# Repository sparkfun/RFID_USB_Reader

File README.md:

SparkFun RFID USB Reader
=========================

[*SparkFun RFID USB Reader (SEN-09963)*](https://www.sparkfun.com/products/9963)

The SparkFun RFID USB Reader is a simple to use, USB to serial base unit for the ID-3LA, ID-12LA, and ID-20LA readers.

Documentation
-------------
- **[Hookup Guide](https://learn.sparkfun.com/tutorials/sparkfun-rfid-starter-kit-hookup-guide)** - The hookup guide for the SparkFun RFID USB Reader

Repository Contents
-------------------
- **[/Hardware](/Hardware/)** - Hardware design files (.brd, .sch)
- **[/Production](/Production/)** - Production files

Product Variants
----------------
- [SEN-28020](https://www.sparkfun.com/sparkfun-rfid-usb-c-reader.html) - USB-C connector and CH340C converter
- [SEN-09963](https://www.sparkfun.com/sparkfun-rfid-usb-reader.html) - Original product *(w/ USB mini-B connector and FTDI converter)*

Version History
---------------
- [v10](https://github.com/sparkfun/RFID_USB_Reader/releases/tag/v10) - Initial Release

License Information
-------------------

This product is ***open source***!

Please review the [`LICENSE.md`](./LICENSE.md) file for license information.

If you have any questions or concerns about licensing, please contact technical support on our [SparkFun forums](https://forum.sparkfun.com/viewforum.php?f=152).

Distributed as-is; no warranty is given.

- Your friends at SparkFun.

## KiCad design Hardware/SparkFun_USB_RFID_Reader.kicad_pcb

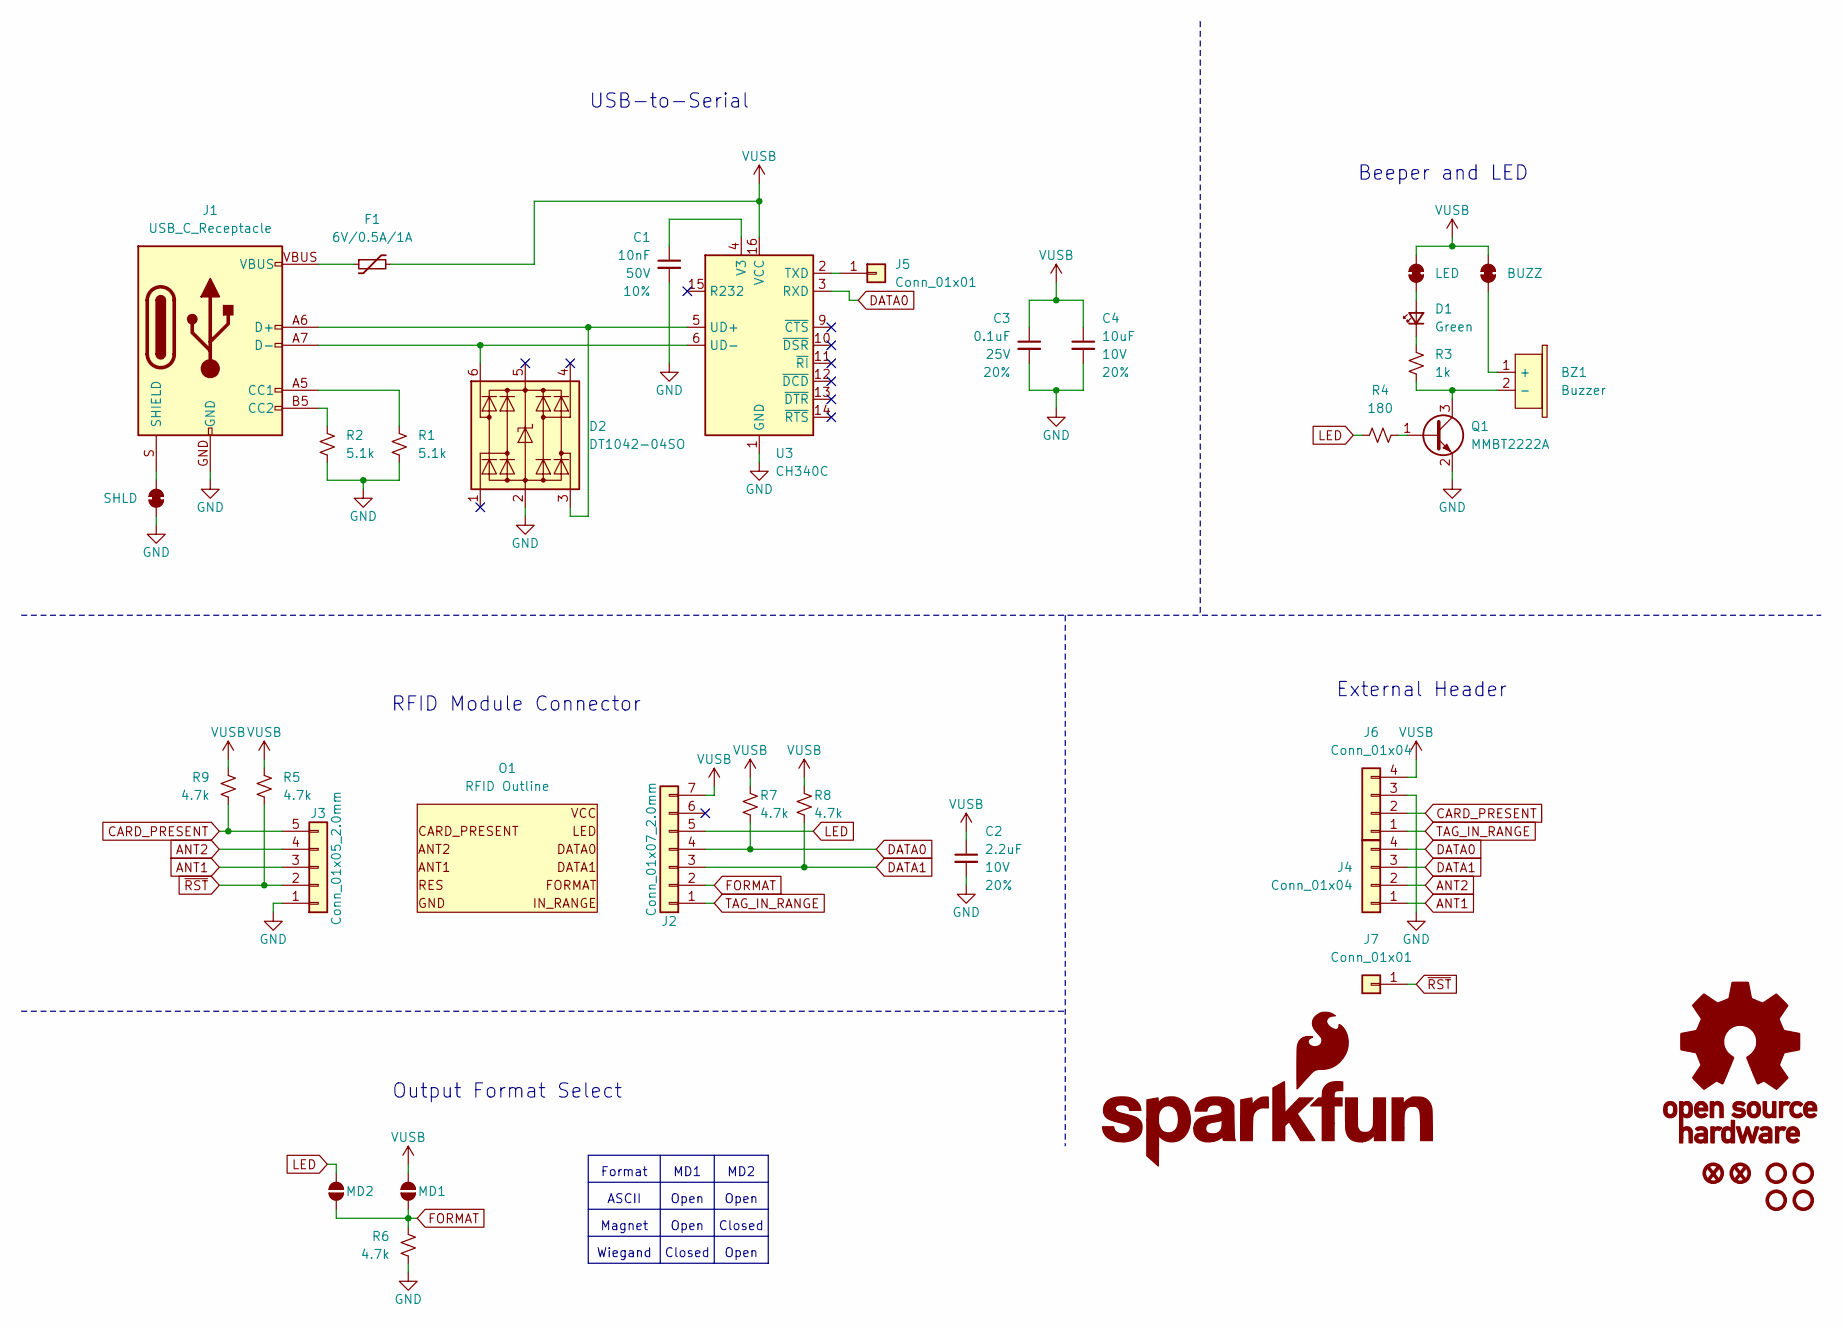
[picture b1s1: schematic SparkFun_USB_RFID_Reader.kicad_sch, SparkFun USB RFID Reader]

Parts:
BZ1: Buzzer; Buzzer_9mm_SMD
C1: 10nF; C_0603_1608Metric; Voltage 50V; Tolerance 10%
C2: 2.2uF; C_0603_1608Metric; Voltage 10V; Tolerance 20%
C3: 0.1uF; C_0603_1608Metric; Voltage 25V; Tolerance 20%
C4: 10uF; C_0603_1608Metric; Voltage 10V; Tolerance 20%
D1: Green; LED_0603_1608Metric_Green
D2: DT1042-04SO; SOT23-6
F1: 6V/0.5A/1A; 0805
FID1, FID4: Fiducial_0.5mm; Fiducial_0.5mm_Mask1mm
G1: SparkFun_Logo
G2: OSHW_Logo; Creative_Commons_License
J1: USB_C_Receptacle; USB-C_16
J2: Conn_01x07_2.0mm; 1x07_2.0mm
J3: Conn_01x05_2.0mm; 1x05_2.0mm
J4, J6: Conn_01x04; 1x04
J5, J7: Conn_01x01; 1x01
JP1: BUZZ; Jumper_2_NC_Trace
JP2: LED; Jumper_2_NC_Trace
JP3: SHLD; Jumper_2_NC_Trace
JP5: MD1; Jumper_2_NO
JP7: MD2; Jumper_2_NO
O1: RFID Outline; ID-2_12_20_Outline
Q1: MMBT2222A; SOT23-3
R1, R2: 5.1k; R_0603_1608Metric
R3: 1k; R_0603_1608Metric
R4: 180; R_0603_1608Metric
R5, R6, R7, R8, R9: 4.7k; R_0603_1608Metric
ST1, ST2, ST3, ST4: Standoff
U3: CH340C; SO-16

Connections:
ANT1: J3.3, J4.1
ANT2: J3.4, J4.2
CARD_PRESENT: J3.5, J6.2, R9.1
DATA0: J2.4, J4.4, R7.1, U3.3 (RXD)
DATA1: J2.3, J4.3, R8.1
FORMAT: J2.2, JP5.1 (A), JP7.1 (A), R6.2
GND: C1.2, C2.2, C3.2, C4.2, D2.2 (GND), J1.GND, J3.1, J6.3, JP3.1 (A), Q1.2 (E), R1.1, R2.1, R6.1, U3.1 (GND)
LED: J2.5, JP7.2 (B), R4.1
unnamed: BZ1.1 (+), JP1.1 (A)
unnamed: BZ1.2 (-), Q1.3 (C), R3.1
unnamed: D1.2 (A), JP2.1 (A)
unnamed: D1.1 (K), R3.2
unnamed: D2.3 (I/O2), J1.A6 (D+), J1.B6 (D+), U3.5 (UD+)
unnamed: D2.6 (I/O4), J1.A7 (D-), J1.B7 (D-), U3.6 (UD-)
unnamed: F1.1, J1.VBUS
unnamed: J1.A5 (CC1), R1.2
unnamed: J1.B5 (CC2), R2.2
unnamed: J1.S (SHIELD), JP3.2 (B)
unnamed: J5.1, U3.2 (TXD)
unnamed: Q1.1 (B), R4.2
unnamed: C1.1, U3.4 (V3)
TAG_IN_RANGE: J2.1, J6.1
VUSB: C2.1, C3.1, C4.1, F1.2, J2.7, J6.4, JP1.2 (B), JP2.2 (B), JP5.2 (B), R5.2, R7.2, R8.2, R9.2, U3.16 (VCC)
~RST: J3.2, J7.1, R5.1

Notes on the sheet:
MD1
Magnet
MD2
Closed
Beeper and LED
Open
USB-to-Serial
External Header
RFID Module Connector
Output Format Select
ASCII
Format
Wiegand

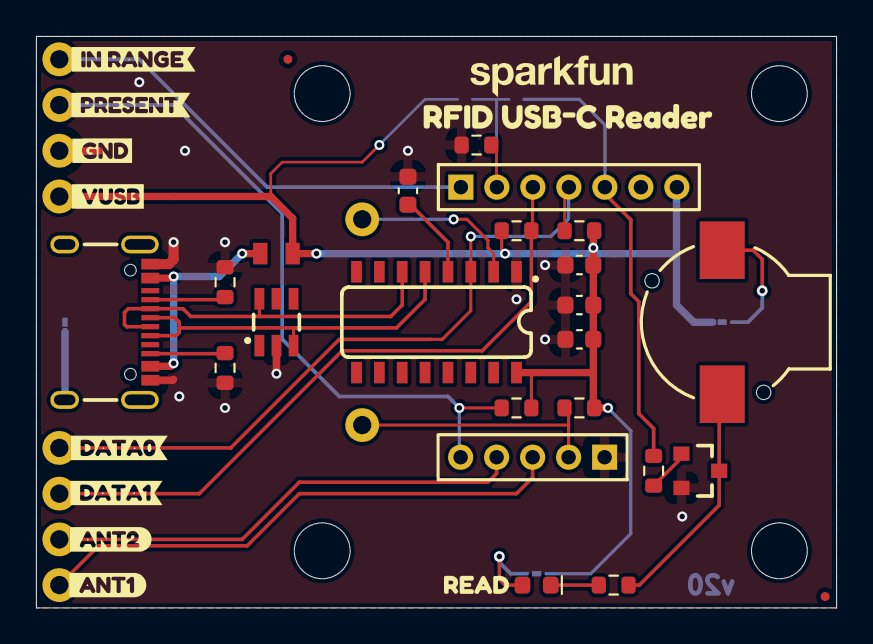
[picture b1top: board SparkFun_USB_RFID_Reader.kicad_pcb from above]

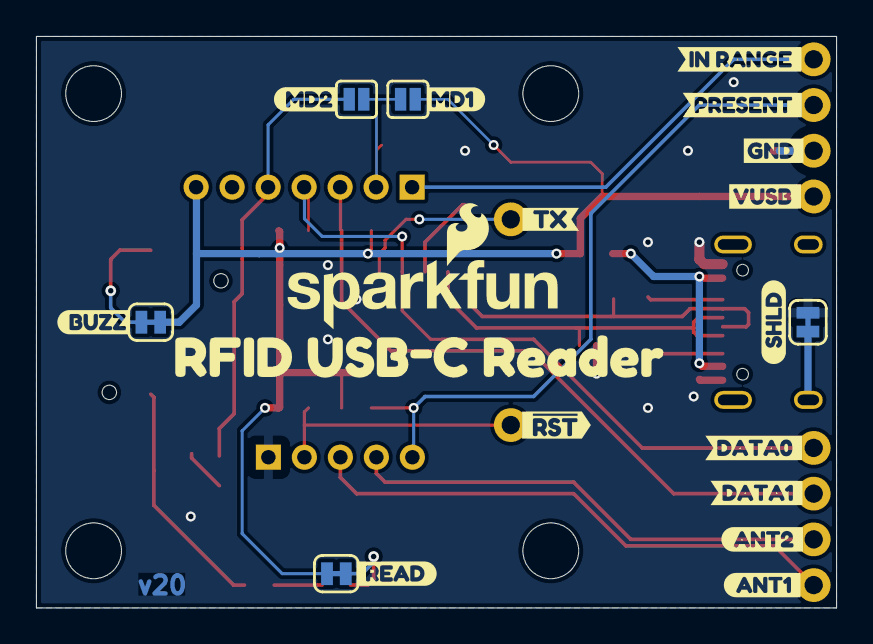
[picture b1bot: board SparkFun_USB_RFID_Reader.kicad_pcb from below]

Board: 2 copper layers, 44.5 x 31.8 mm, 65 parts (21 on the bottom side), 24 nets.

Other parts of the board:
kibuzzard-67A3BA96: G***; kibuzzard-67A3BA96
kibuzzard-67A3BC63: G***; kibuzzard-67A3BC63
kibuzzard-67A3C4EF: G***; kibuzzard-67A3C4EF
kibuzzard-67A3C6A9: G***; kibuzzard-67A3C6A9
kibuzzard-67A3C6BA: G***; kibuzzard-67A3C6BA
kibuzzard-67A3C6C4: G***; kibuzzard-67A3C6C4
kibuzzard-67A3C6D3: G***; kibuzzard-67A3C6D3
kibuzzard-67A3C54B: G***; kibuzzard-67A3C54B
kibuzzard-67A3C61F: G***; kibuzzard-67A3C61F
kibuzzard-67A3C62C: G***; kibuzzard-67A3C62C
kibuzzard-67A3C66D: G***; kibuzzard-67A3C66D
kibuzzard-67A3C67B: G***; kibuzzard-67A3C67B
kibuzzard-67A3C68A: G***; kibuzzard-67A3C68A
kibuzzard-67A3C68E: G***; kibuzzard-67A3C68E
kibuzzard-67A3C76D: G***; kibuzzard-67A3C76D
kibuzzard-67A3C77D: G***; kibuzzard-67A3C77D
kibuzzard-67A3C99A: G***; kibuzzard-67A3C99A
kibuzzard-67A3C602: G***; kibuzzard-67A3C602
kibuzzard-67A3C638: G***; kibuzzard-67A3C638
kibuzzard-67A3C648: G***; kibuzzard-67A3C648
kibuzzard-67A3C651: G***; kibuzzard-67A3C651
kibuzzard-67A3C660: G***; kibuzzard-67A3C660
kibuzzard-67A3C696: G***; kibuzzard-67A3C696
kibuzzard-67A3C764: G***; kibuzzard-67A3C764
kibuzzard-67A3C793: G***; kibuzzard-67A3C793
kibuzzard-67A3C992: G***; kibuzzard-67A3C992

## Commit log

2015-03-10 Adding hardware files, updating README
2019-12-05 revising to move plane and routing out from underneath of RFID reader, removing ant pin breakout
2019-12-06 post checklist changes
2019-12-06 post review changes
2019-12-09 post QC checklist changes
2019-12-09 changing name to USB-C
2019-12-17 updating Buzzer and npn transistor to have PROD_ID
2025-01-09 v20 Ready for Review
    - Move design to KiCad
    - Push all connectors to one side of the board
    - Round dimensions to nearest 0.25"
    - Update to USB-C
    - Swap out FTDI for CH340
    - Center RFID module in 1" CTC mounting holes
2025-01-10 Get rid of backups
2025-01-10 Update to small symbols. Add RFID outline device.
2025-01-10 Add fiducials. Add logos. Letter size.
2025-01-10 Add 3D models
2025-01-10 Rename files
2025-01-21 Center USB-C Connector
    - Move USB-C connector to center
    - Arrange 0.1" headers to either side
2025-01-21 Move fiducial from silk. Add version in copper. Move OSHW gear from silk.
2025-01-21 Reduce to two layer board
2025-01-21 Add panel files
2025-01-21 Align silk labels
2025-01-21 Change decoupling cap. Change LED resistor.
2025-01-21 Fix DRC error
2025-01-23 Change to PTH connectors
2025-02-05 Post design review fixes
2025-02-05 Remove old files.
2025-03-14 Link hookup guide
2025-03-20 Update template files
2025-03-20 Update README.md
    Update file format
    Add new product variant

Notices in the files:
parts and their libraries:
https://creativecommons.org/licenses/by-sa/4.0
Released under the Creative Commons Attribution Share-Alike 4.0 License
